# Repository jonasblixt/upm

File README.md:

## UPM - USB Power Monitor

This device monitors current and voltage for USB powered devices.

# Hardware

Assembled PCB 

The PCB is a four layer board, manufactured by OSH Park. The boards can
 be ordered [here](https://oshpark.com/shared_projects/uE5lZDkP)

Schematics, layout and BOM can be found [here](https://github.com/jonpe960/upm/tree/master/hw/Release/R1)

# System description

The device has a built in, two port, USB hub. One of the down stream ports
connects to the USB A connector and the other down stream port is connected to
the microcontroller.

An integrade analog frontend that contains a 16 bit ADC and differential
amplifier measures the voltage and current of the down stream VBUS supply. Three
auxillary diff inputs are available on a pin header.

It is possible to control the output VBUS with the on board power switch, which
also has built in short circuit protection. Three auxillary, open collector,
outputs are available on pin header.

# Ncurses TUI

The ncurses based TUI, displaying voltage, current and energy usage. 
Outputs can be controled from the TUI:
 - A/a VBUS on/off
 - S/s out1 on/off
 - D/d out2 on/off
 - F/f out3 on/off
 - r Reset energy counters

# Intended usage

This project came from a need to remotley monitor and power cycle USB powered devices.

# Future improvements

 - Add domain/tcp socket listener for remote control
 - Support for logging

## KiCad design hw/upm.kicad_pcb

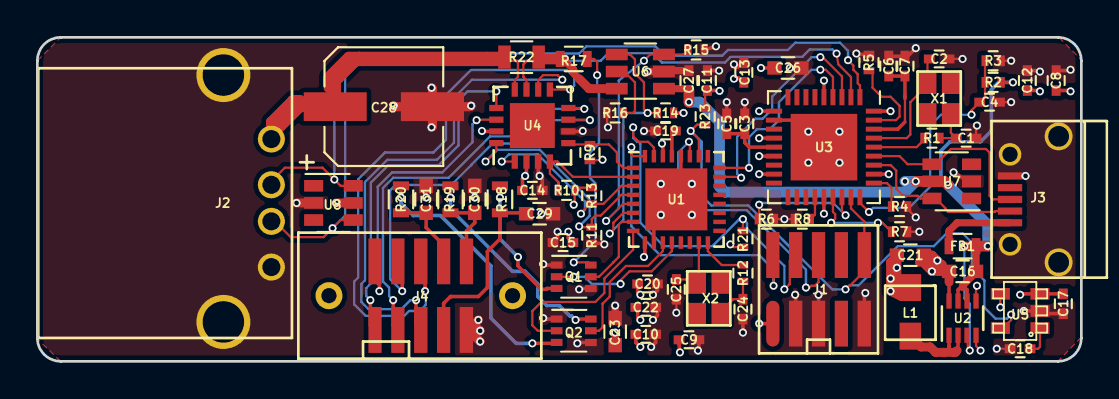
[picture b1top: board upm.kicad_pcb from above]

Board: 4 copper layers, 58.0 x 18.0 mm, 72 parts (0 on the bottom side), 57 nets.

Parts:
C1, C2, C24, C25: C0402_12p_25Vdc_C0G_2; C0402
C3, C6, C18: C0402_100n_25Vdc_X7R; C0402
C4, C5, C7, C8, C9, C10, C11, C12, C13, C14, C15, C17, C19, C20, C22, C27: C0402_1u_6.3Vdc_X7R; C0402
C16, C21, C23, C26: C0603_10u_10Vdc_X7R; C0603
C28: PCAP_120u_4; CP_Elec_6.3x5.8
C29, C30, C31: C0603_22n_100Vdc_X7R; C0603
FB1: BL0603_BLM18BB121SN1D; L0603
J1: FTSH-105-01-F-DV-K
J2: USB_A_292303-1; USB_A_TH
J3: DX4R005JJ2R1800; USB_Micro-B
J4: TFM-105-02-S-D-WT
L1: IHLP1212_1u_1; IHLP1212
Q1, Q2: PUMH13; SOT-363_SC-70-6
R1, R12: R0402_100R; R0402
R2, R3, R4, R6, R7, R8, R11, R13, R14, R15, R23: R0402_46k40; R0402
R5: R0402_12k10; R0402
R9, R10: R0402_2k20; R0402
R16: R0402_21k; R0402
R17: R0603_200R; R0603
R18, R19, R20: R0603_51R; R0603
R21: R0402_1k; R0402
R22: R0805_0R1; R0805
U1: ATSAMD21E15B; QFN-32-1EP_5x5mm_Pitch0.5mm
U2: MIC23150-SYMT; DFN-8_2x2mm_Pitch0.5mm
U3: USB2512B; QFN-36-1EP_6x6mm_Pitch0.5mm
U4: PAC1934; QFN-16-1EP_4x4mm_Pitch0.65mm
U5: LP3470IM5X-3.08_NOPB; SOT-23-5
U6: NCP380HSNAJAAT1G; TSOT-23-6
U7, U8: USBLC6-4; SOT-23-6
X1: NX2520SA-24.000000MHZ; NX2520SA
X2: NX2520SA-16.000000MHZ; NX2520SA

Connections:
/DUT_DISCHARGE: Q1.2, U1.12
/DUT_USB_D_N: J2.2, U3.1, U8.6
/DUT_USB_D_P: J2.3, U3.2, U8.4
/DUT_USB_EN: R15.2, U1.5, U6.3
/DUT_USB_FLAG_N: R14.1, U1.6, U6.4
/DUT_USB_VBUS: C28.1, J2.1, R22.1, U4.12, U8.5
/I2C_SCL: R10.2, U1.2, U4.4
/I2C_SDA: R9.2, U1.1, U4.5
/OUT1_EN: Q1.5, U1.7
/OUT2_EN: Q2.2, U1.8
/OUT3_EN: Q2.5, U1.11
/PAC_ALERT_N: R13.1, U1.3, U4.1
/PAC_PWRDN_N: R11.2, U1.4, U4.16
/RST_N: J1.10, R23.1, U1.26, U3.26, U5.5
/SNS2_N: J4.9, U4.14
/SNS2_P: J4.10, U4.13
/SNS3_N: J4.7, U4.7
/SNS3_P: J4.8, U4.8
/SNS4_N: J4.5, U4.9
/SNS4_P: J4.6, U4.10
/SWCLK: J1.4, R21.2, U1.31
/SWDIO: J1.2, U1.32
/SWO: J1.6, U1.27
/UC_USB_D_N: U1.23, U3.3
/UC_USB_D_P: U1.24, U3.4
/USB_D_N: J3.2, U3.30, U7.6
/USB_D_P: J3.3, U3.31, U7.4
/VDDCORE: C19.1, U1.29
/XTAL_IN: C25.1, U1.15, X2.3
/XTAL_OUT: R12.2, U1.16
GND: C1.2, C2.2, C3.2, C4.2, C5.2, C6.2, C7.2, C8.2, C9.2, C10.2, C11.2, C12.2, C13.2, C14.2, C15.2, C16.2, C17.2, C18.2, C19.2, C20.2, C21.2, C22.2, C23.2, C24.2, C25.2, C26.2, C27.2, C28.2, C29.2, C30.2, C31.2, J1.3, J1.5, J1.9, J2.4, J2.5, J2.6, J3.5, J3.6, J3.7, J4.2, Q1.1, Q1.4, Q2.1, Q2.4, R3.1, R4.2, R5.2, R6.1, R7.1, R8.1, R11.1, R15.1, R16.2, U1.10, U1.28, U1.33, U2.5, U2.8, U3.11, U3.37, U4.3, U4.6, U5.2, U6.2, U7.2, U8.2
unnamed: C1.1, R1.2, X1.1
unnamed: C2.1, U3.33, X1.3
unnamed: C3.1, C5.1, U3.14
unnamed: C4.1, R2.1, R3.2, U3.27
unnamed: C6.1, C7.1, U3.34
unnamed: C18.1, U5.1
unnamed: C24.1, R12.1, X2.1
unnamed: C29.1, J4.4, R18.1
unnamed: C30.1, J4.1, R19.1
unnamed: C31.1, J4.3, R20.1
unnamed: FB1.1, J3.1
unnamed: L1.1, U2.1, U2.2
unnamed: Q1.3, R18.2
unnamed: Q1.6, R17.2
unnamed: Q2.3, R20.2
unnamed: Q2.6, R19.2
unnamed: R1.1, U3.32
unnamed: R4.1, U3.28
unnamed: R5.1, U3.35
unnamed: R6.2, U3.25
unnamed: R7.2, U3.24
unnamed: R8.2, U3.22
unnamed: R16.1, U6.5
unnamed: R17.1, R22.2, U4.11, U6.6
P3V3: C8.1, C9.1, C10.1, C11.1, C12.1, C13.1, C14.1, C15.1, C17.1, C20.1, C21.1, C22.1, C23.1, C26.1, J1.1, L1.2, R9.1, R10.1, R13.2, R14.2, R21.1, R23.2, U1.9, U1.30, U2.4, U3.5, U3.10, U3.13, U3.15, U3.17, U3.23, U3.29, U3.36, U4.2, U4.15, U5.3, U5.4
P5V0: C16.1, C27.1, FB1.2, R2.2, U2.3, U2.6, U2.7, U6.1, U7.5

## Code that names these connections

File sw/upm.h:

/**
 * UPM
 *
 * Copyright (C) 2018 Jonas Persson <jonpe960@gmail.com>
 *
 * SPDX-License-Identifier: BSD-3-Clause
 *
 */

#ifndef __UPM_H__
#define __UPM_H__

#define PIN_SDA            PIN_PA0
#define PIN_SCL            PIN_PA1
#define PIN_PAC_ALERT_N    PIN_PA2
#define PIN_PACPWRDN_N     PIN_PA3
#define PIN_DUT_USB_EN     PIN_PA4
#define PIN_DUT_USB_FLAG_N PIN_PA5
#define PIN_OUT1_EN        PIN_PA6
#define PIN_OUT2_EN        PIN_PA7
#define PIN_OUT3_EN        PIN_PA8
#define PIN_DUT_DISCHARGE  PIN_PA9
#define PIN_XTAL_IN        PIN_PA14
#define PIN_XTAL_OUT       PIN_PA15
#define PIN_USB_DM         PIN_PA24
#define PIN_USB_DP         PIN_PA25
#define PIN_SWO            PIN_PA28
#define PIN_SWCLK          PIN_PA30
#define PIN_SWDIO          PIN_PA31

#define UNUSED_PINS (   PIN_PA10 | \
                        PIN_PA11 | \
                        PIN_PA16 | \
                        PIN_PA17 | \
                        PIN_PA18 | \
                        PIN_PA19 | \
                        PIN_PA22 | \
                        PIN_PA23 | \
                        PIN_PA27)

#endif

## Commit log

2018-09-04 Initial structure
2018-09-04 Added some datasheets
2018-09-13 R1 release of HW
2018-09-13 Removed DS_store -files
2018-09-14 Added BOM
2018-09-15 Updated gitignore
2018-12-09 First working version
2018-12-09 Updated documentation
2018-12-09 Added licensing info
2019-01-15 Added timeout, under some circumstances the USB link can break down. Unless there is a timeout the device will be stuck for ever.
